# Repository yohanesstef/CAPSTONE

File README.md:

# Wireless Power Transfer - CAPSTONE Project

This is repository for a Wireless Power Transfer. I have completed this project in semester 6 as an assignment for the CAPSTONE course. In this repository there are three PCB board that I design using KiCad 7.0. The boards are 12V Fullbridge Inverter, transmitter-board, and receiver-board. 
## Important notes !!!
This repository file management maybe kinda messy. But you can find 12V Fullbridge inside the directory:
```bash
.\full-bridge-inverter\full-bridge-inverter
```
That directory also includes Proteus simulation and source code for Arduino Nano.

Transmitter-board inside the directory:
```bash
.\transmitter-board
```
and receiver-board inside the directory:
```bash
.\receiver-board
```
## 1. 12V Fullbridge Inverter
This full-bridge inverter can convert 12VDC to 12VAC with a frequency ranging from 80kHz to 200kHz. This inverter is controlled by an Arduino Nano as the PWM generator. On the bottom left side of the board, you can adjust the frequency, and the value will be shown on the 0.91-inch OLED display.
### Simulation
Below is the simulation at maximum frequency (200kHz):

Below is the simulation at minimum frequency (80kHz):

### Schematic

### Layout

### Board Image

### Specification
| Input Voltage | Output Voltage | Max Output Current | Operating Frequency |
| :---: | :---: | :---: | :---: |
| 5VDC - 15VDC | 7VAC - 15VAC | 3A | 80kHz - 200kHz* |

*operating frequency can be changed by program up to 1MHz
## 2. Transmitter Board
This transmitter board uses an LC series connection. This configuration helps reduce its impedance so the current flow can be maximized. The capacitor can be added or replaced with another one since the board uses an XT30 connector for the capacitor. The capacitor value needs to be calculated based on the resonant frequency to achieve maximum power transfer.

### Schematic

### Layout

### Board Image

## 3. Receiver Board
This receiver board is similar to the transmitter board. The difference is that the receiver board uses an LC parallel connection to minimize its impedance and behave like a purely resistive circuit.
### Schematic

### Layout

### Board Image

Do contact me if you have some question or want to colaborate with me.

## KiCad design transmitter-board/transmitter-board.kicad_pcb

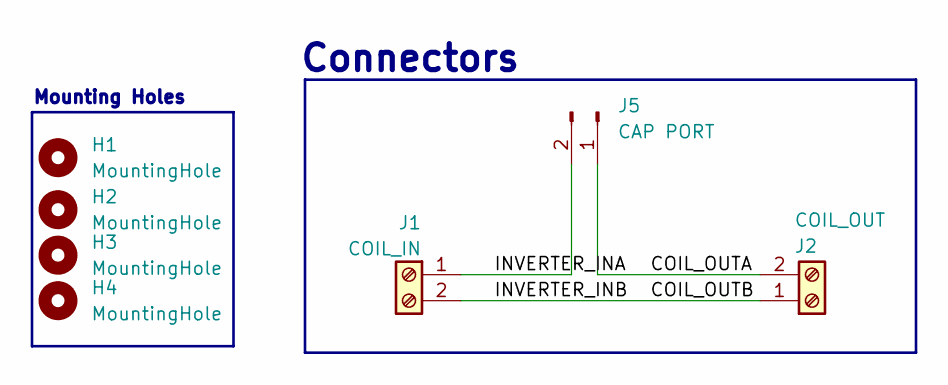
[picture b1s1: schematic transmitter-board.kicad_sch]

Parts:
H1, H2, H3, H4: MountingHole; MountingHole_3.2mm_M3
J1: COIL_IN; HB9500
J2: COIL_OUT; HB9500
J5: CAP PORT; AMASS_XT60-M_1x02_P7.20mm_Vertical

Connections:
/COIL_OUTA: J2.2, J5.1
/COIL_OUTB: J1.2, J2.1
/INVERTER_INA: J1.1, J5.2

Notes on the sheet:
Connectors
Mounting Holes

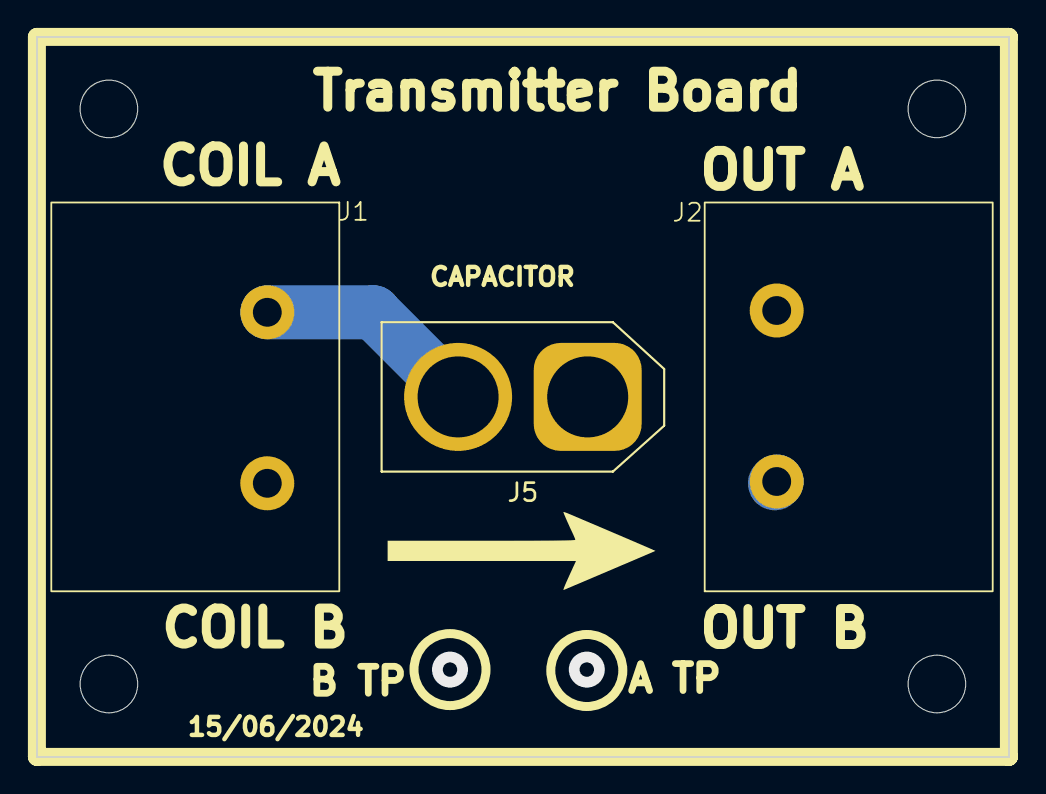
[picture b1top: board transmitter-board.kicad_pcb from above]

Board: 2 copper layers, 54.0 x 40.0 mm, 7 parts (0 on the bottom side), 3 nets.

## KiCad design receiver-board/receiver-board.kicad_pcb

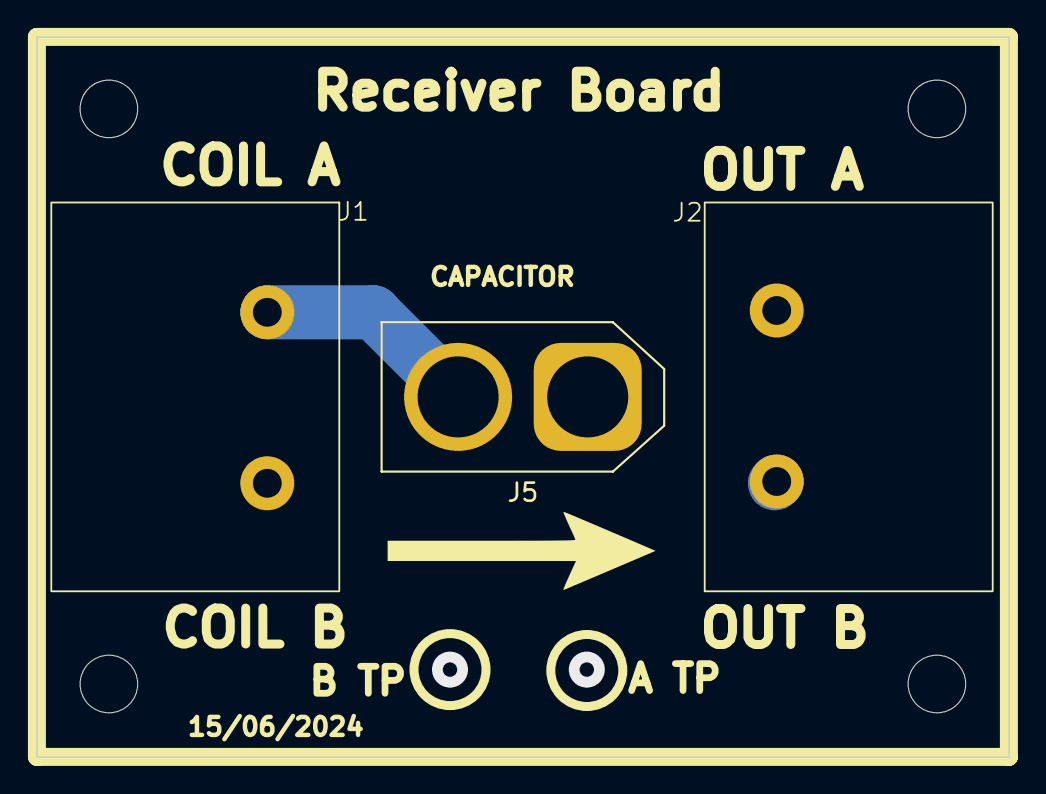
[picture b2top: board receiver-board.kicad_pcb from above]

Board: 2 copper layers, 54.0 x 40.0 mm, 7 parts (0 on the bottom side), 2 nets.

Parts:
H1, H2, H3, H4: MountingHole; MountingHole_3.2mm_M3
J1, J2: Screw_Terminal_01x02; HB9500
J5: Conn_01x02_Pin; AMASS_XT60-M_1x02_P7.20mm_Vertical

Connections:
/COIL_OUTA: J1.1, J2.2, J5.2
/COIL_OUTB: J1.2, J2.1, J5.1

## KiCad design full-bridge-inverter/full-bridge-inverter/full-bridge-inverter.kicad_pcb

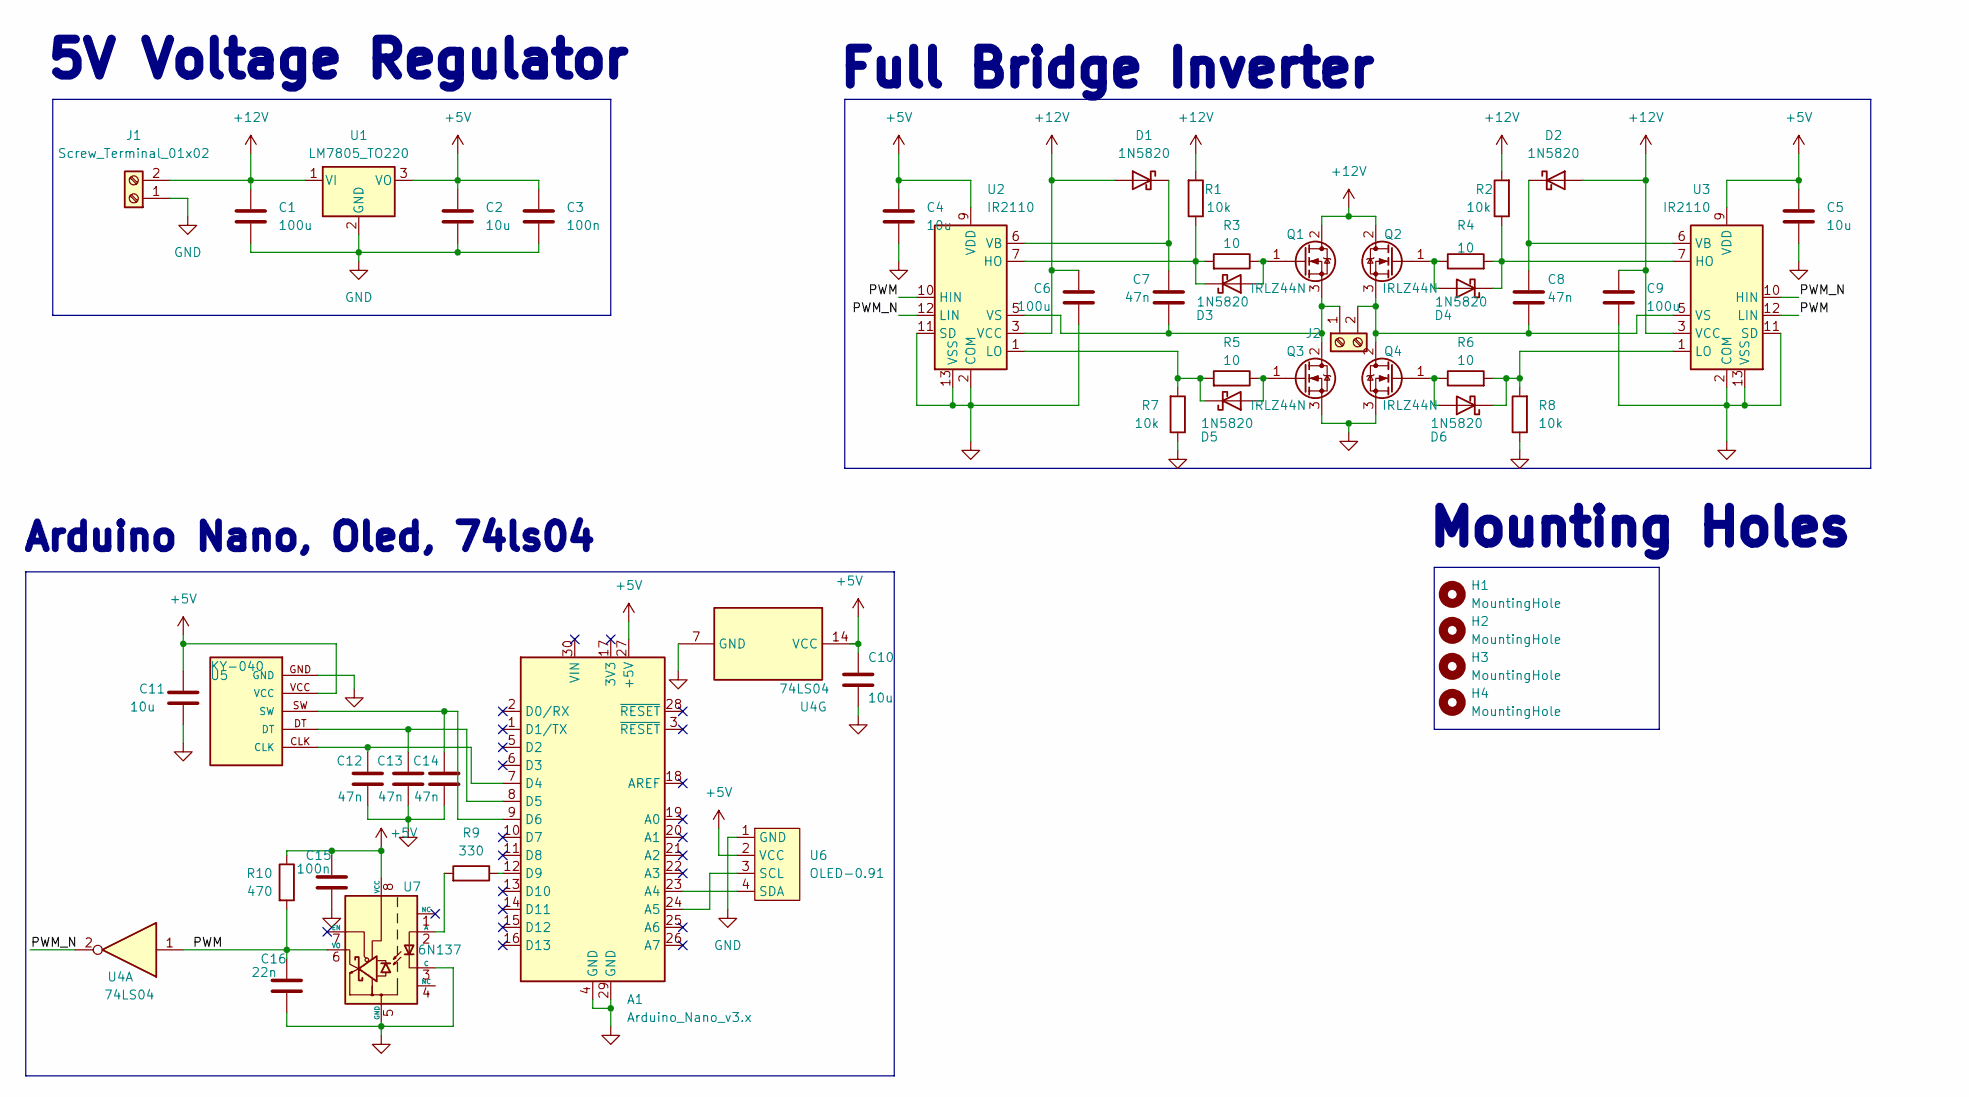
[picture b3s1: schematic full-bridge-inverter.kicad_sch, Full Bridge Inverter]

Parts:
A1: Arduino_Nano_v3.x; Arduino_Nano_v2
C1, C6, C9: 100u; C_Radial_D8.0mm_H11.5mm_P3.50mm
C2, C4, C5, C10, C11: 10u; C_Radial_D5.0mm_H11.0mm_P2.00mm
C3, C15: 100n; C_Disc_D4.3mm_W1.9mm_P5.00mm
C7, C8: 47n; C_Disc_D3.0mm_W1.6mm_P2.50mm
C12, C13, C14: 47n; C_Disc_D4.3mm_W1.9mm_P5.00mm
C16: 22n; C_Disc_D4.3mm_W1.9mm_P5.00mm
D1, D2, D3, D4, D5, D6: 1N5820; D_DO-201AD_P15.24mm_Horizontal
H1, H2, H3, H4: MountingHole; MountingHole_3.2mm_M3_DIN965
J1, J2: Screw_Terminal_01x02; HB9500
Q1, Q2, Q3, Q4: IRLZ44N; TO-220-3_Vertical
R1, R2, R7, R8: 10k; R_Axial_DIN0411_L9.9mm_D3.6mm_P12.70mm_Horizontal
R3, R4, R5, R6: 10; R_Axial_DIN0411_L9.9mm_D3.6mm_P12.70mm_Horizontal
R9: 330; R_0805_2012Metric
R10: 470; R_0805_2012Metric
U1: LM7805_TO220; TO-220-3_Vertical
U2, U3: IR2110; DIP-14_W7.62mm_Socket_LongPads
U4: 74LS04; DIP-14_W7.62mm_Socket_LongPads
U5: KY-040; KY-040-PORT
U6: OLED-0.91; SSD1306-0.91-OLED-4pin-128x32
U7: 6N137; DIP-8_W7.62mm

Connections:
+5V: A1.27 (+5V), C2.1, C3.1, C4.1, C5.1, C10.1, C11.1, C15.1, R10.1, U1.3 (VO), U2.9 (VDD), U3.9 (VDD), U4.14 (VCC), U5.VCC, U6.2 (VCC), U7.8 (VCC)
+12V: C1.1, C6.1, C9.1, D1.2 (A), D2.2 (A), J1.2, Q1.2 (D), Q2.2 (D), R1.2, R2.2, U1.1 (VI), U2.3 (VCC), U3.3 (VCC)
/PWM: C16.1, R10.2, U2.10 (HIN), U3.12 (LIN), U4.1, U7.6 (VO)
/PWM_N: U2.12 (LIN), U3.10 (HIN), U4.2
GND: A1.4 (GND), A1.29 (GND), C1.2, C2.2, C3.2, C4.2, C5.2, C6.2, C9.2, C10.2, C11.2, C12.2, C13.2, C14.2, C15.2, C16.2, J1.1, Q3.3 (S), Q4.3 (S), R7.1, R8.1, U1.2 (GND), U2.2 (COM), U2.11 (SD), U2.13 (VSS), U3.2 (COM), U3.11 (SD), U3.13 (VSS), U4.7 (GND), U5.GND, U6.1 (GND), U7.3 (C), U7.5 (GND)
unnamed: A1.23 (A4), U6.4 (SDA)
unnamed: A1.24 (A5), U6.3 (SCL)
unnamed: A1.7 (D4), C12.1, U5.CLK
unnamed: A1.8 (D5), C13.1, U5.DT
unnamed: A1.9 (D6), C14.1, U5.SW
unnamed: A1.12 (D9), R9.1
unnamed: C7.1, D1.1 (K), U2.6 (VB)
unnamed: C8.1, D2.1 (K), U3.6 (VB)
unnamed: D3.2 (A), Q1.1 (G), R3.1
unnamed: D3.1 (K), R1.1, R3.2, U2.7 (HO)
unnamed: D4.2 (A), Q2.1 (G), R4.1
unnamed: D4.1 (K), R2.1, R4.2, U3.7 (HO)
unnamed: D5.2 (A), Q3.1 (G), R5.1
unnamed: D5.1 (K), R5.2, R7.2, U2.1 (LO)
unnamed: D6.2 (A), Q4.1 (G), R6.1
unnamed: D6.1 (K), R6.2, R8.2, U3.1 (LO)
unnamed: C7.2, J2.1, Q1.3 (S), Q3.2 (D), U2.5 (VS)
unnamed: C8.2, J2.2, Q2.3 (S), Q4.2 (D), U3.5 (VS)
unnamed: R9.2, U7.2 (A)

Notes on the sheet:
Arduino Nano, Oled, 74ls04
Full Bridge Inverter
Mounting Holes
5V Voltage Regulator

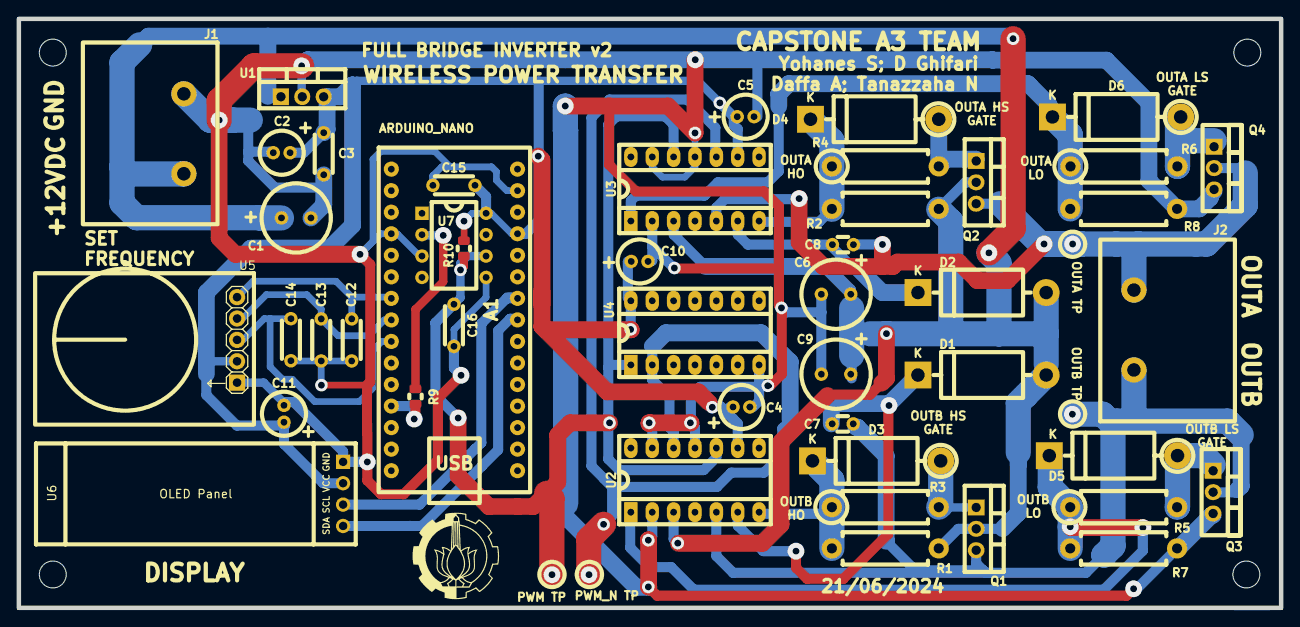
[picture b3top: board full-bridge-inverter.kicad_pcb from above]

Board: 2 copper layers, 150.0 x 70.0 mm, 50 parts (0 on the bottom side), 24 nets.

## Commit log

2024-08-02 init
2024-08-04 add receiver board
2024-08-05 add inverter simulation
2024-08-05 add source code
